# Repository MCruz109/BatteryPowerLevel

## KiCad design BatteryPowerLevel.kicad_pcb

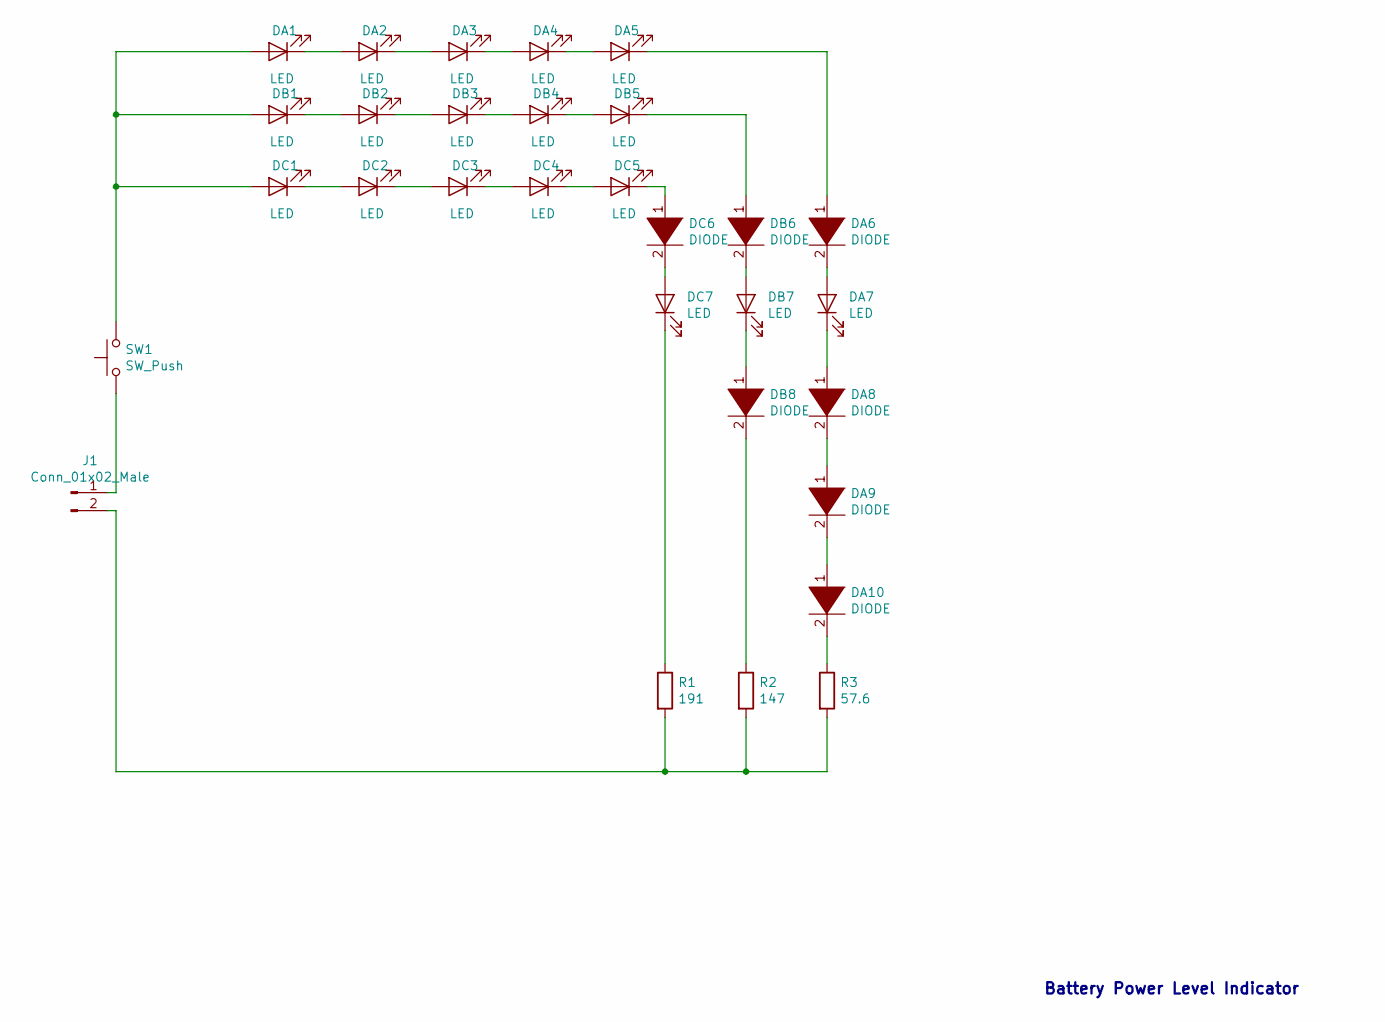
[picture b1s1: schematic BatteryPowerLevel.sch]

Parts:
DA1, DA2, DA3, DA4, DA5: LED; LTST-C191KGKT (LED 2V)
DA6, DA8, DA9, DA10: DIODE; CDSQR400B-HF (Diode 0.77V 10ohms)
DA7: LED; LW514 (LED 3.2V)
DB1, DB2, DB3, DB4, DB5: LED; LTST-C191KGKT (LED 2V)
DB6, DB8: DIODE; CDSQR400B-HF (Diode 0.77V 10ohms)
DB7: LED; LW514 (LED 3.2V)
DC1, DC2, DC3, DC4, DC5: LED; LTST-C191KGKT (LED 2V)
DC6: DIODE; CDSQR400B-HF (Diode 0.77V 10ohms)
DC7: LED; LW514 (LED 3.2V)
J1: Conn_01x02_Male; Connector
R1: 191; RC0402(resistors)
R2: 147; RC0402(resistors)
R3: 57.6; RC0402(resistors)
SW1: SW_Push; Connector

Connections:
unnamed: DA1.1 (K), DA2.2 (A)
unnamed: DA1.2 (A), DB1.2 (A), DC1.2 (A), SW1.2
unnamed: DA2.1 (K), DA3.2 (A)
unnamed: DA3.1 (K), DA4.2 (A)
unnamed: DA4.1 (K), DA5.2 (A)
unnamed: DA5.1 (K), DA6.1 (K)
unnamed: DA6.2 (A), DA7.2 (A)
unnamed: DA7.1 (K), DA8.1 (K)
unnamed: DA8.2 (A), DA9.1 (K)
unnamed: DA9.2 (A), DA10.1 (K)
unnamed: DA10.2 (A), R3.1
unnamed: DB1.1 (K), DB2.2 (A)
unnamed: DB2.1 (K), DB3.2 (A)
unnamed: DB3.1 (K), DB4.2 (A)
unnamed: DB4.1 (K), DB5.2 (A)
unnamed: DB5.1 (K), DB6.1 (K)
unnamed: DB6.2 (A), DB7.2 (A)
unnamed: DB7.1 (K), DB8.1 (K)
unnamed: DB8.2 (A), R2.1
unnamed: DC1.1 (K), DC2.2 (A)
unnamed: DC2.1 (K), DC3.2 (A)
unnamed: DC3.1 (K), DC4.2 (A)
unnamed: DC4.1 (K), DC5.2 (A)
unnamed: DC5.1 (K), DC6.1 (K)
unnamed: DC6.2 (A), DC7.2 (A)
unnamed: DC7.1 (K), R1.1
unnamed: J1.1, SW1.1
unnamed: J1.2, R1.2, R2.2, R3.2

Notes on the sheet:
Battery Power Level Indicator

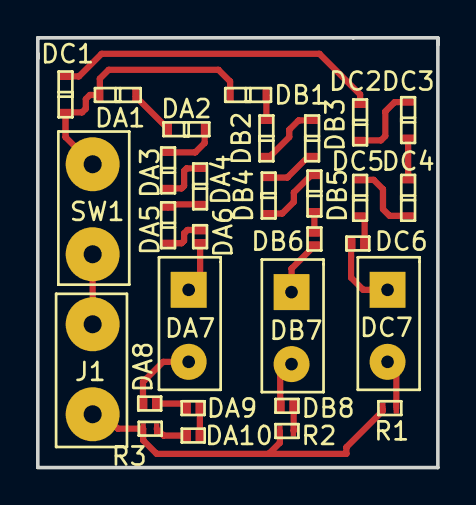
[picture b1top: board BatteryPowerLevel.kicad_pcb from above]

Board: 2 copper layers, 22.2 x 23.9 mm, 30 parts (0 on the bottom side), 28 nets.

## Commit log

2019-03-05 BatteryPowerLevel
2019-03-10 Changed the design
2019-03-10 Reverted
2019-03-10 Revision
